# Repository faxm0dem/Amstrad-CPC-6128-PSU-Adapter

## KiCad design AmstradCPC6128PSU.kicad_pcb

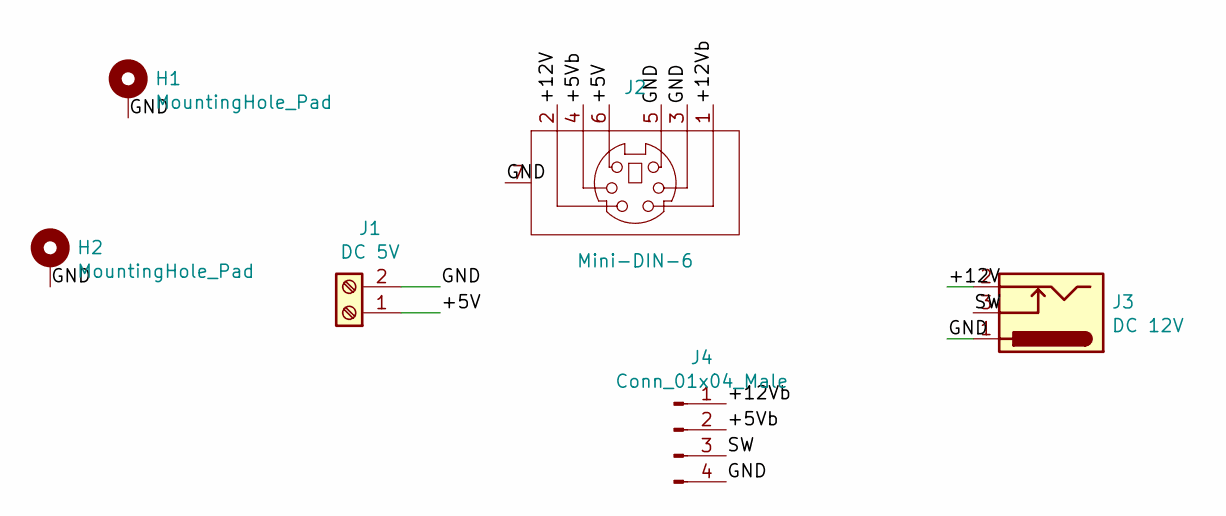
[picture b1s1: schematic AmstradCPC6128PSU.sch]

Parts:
H1, H2: MountingHole_Pad; MountingHole_2.2mm_M2_Pad_Via
J1: DC 5V; TerminalBlock_bornier-2_P5.08mm
J2: Mini-DIN-6; Connector_Mini-DIN_Female_6Pin_2rows
J3: DC 12V; BarrelJack_Horizontal
J4: Conn_01x04_Male; PinHeader_1x04_P2.54mm_Vertical

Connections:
/+5V: J1.1, J2.6
/+5Vb: J2.4, J4.2
/+12V: J2.2, J3.2
/+12Vb: J2.1, J4.1
/GND: H1.1, H2.1, J1.2, J2.3, J2.5, J2.7 (Shell), J3.1, J4.4
/SW: J3.3, J4.3

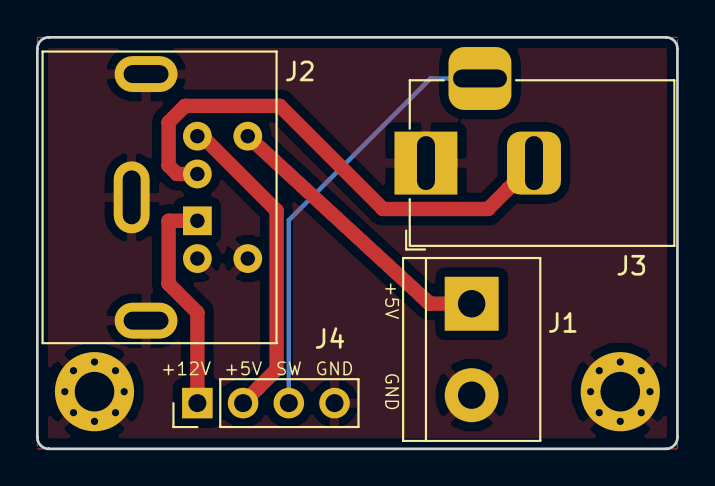
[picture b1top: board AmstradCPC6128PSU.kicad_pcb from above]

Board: 2 copper layers, 35.6 x 22.9 mm, 6 parts (0 on the bottom side), 6 nets.

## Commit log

2020-05-12 init
2020-05-12 kicad is no peace of cake
2020-05-24 hmmm
2020-05-24 getting there
2020-05-24 Swap +5V and GND
2020-05-26 Add gitignore
    Use github provided gitignore
2020-05-26 Add picture of minidin psu
